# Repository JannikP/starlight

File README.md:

# starlight
Art installation to showcase our stellar neighborhood

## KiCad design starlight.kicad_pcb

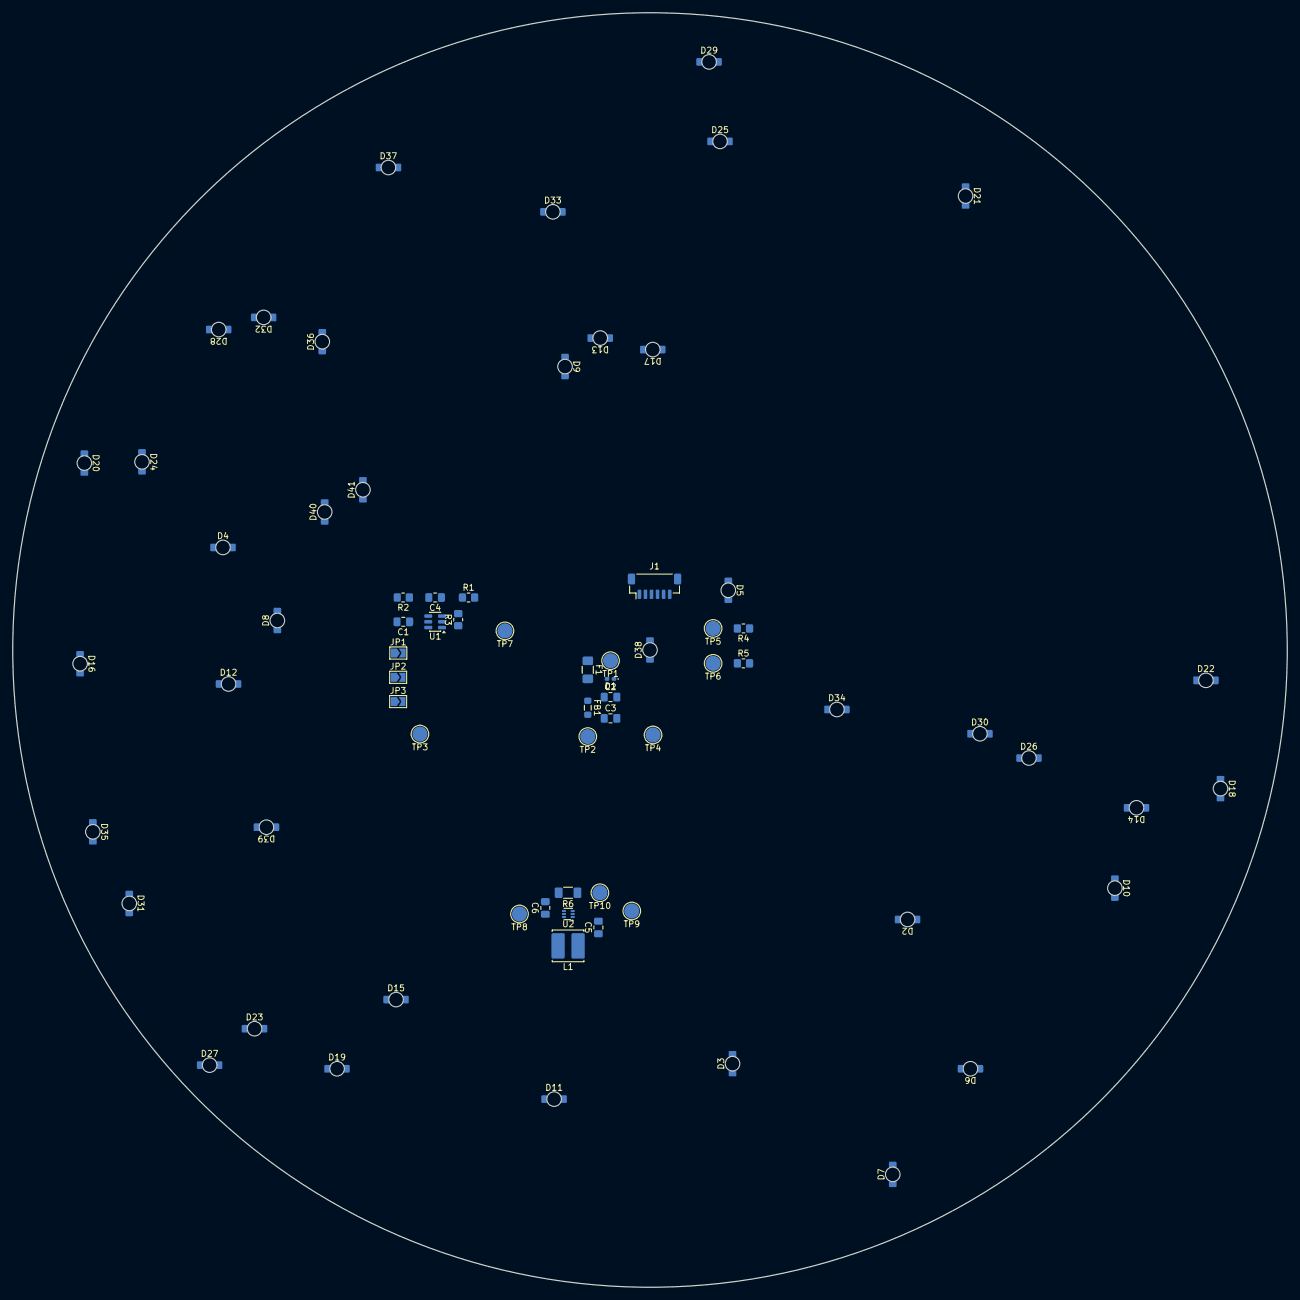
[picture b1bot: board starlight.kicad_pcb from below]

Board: 2 copper layers, 210.0 x 210.0 mm, 72 parts (72 on the bottom side), 50 nets, no tracks yet.

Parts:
C1, C2: 100n; C_0805_2012Metric_Pad1.18x1.45mm_HandSolder
C3, C5: 4µ7; C_0805_2012Metric_Pad1.18x1.45mm_HandSolder
C4: TBD; C_0805_2012Metric_Pad1.18x1.45mm_HandSolder
C6: 1µ; C_0805_2012Metric_Pad1.18x1.45mm_HandSolder
D1: 6V Clamp; D_0402_1005Metric_Pad0.77x0.64mm_HandSolder
D2, D3, D4, D5, D6, D7, D8, D9, D10, D11, D12, D13, D14, D15, D16, D17, D18, D19, D20, D21, D22, D23, D24, D25, D26, D27, D28, D29, D30, D31, D32, D33, D34, D35, D36, D37, D38, D39, D40, D41: Yellow; IN-S124AR-bottom-view
F1: Fuse; Fuse_1206_3216Metric_Pad1.42x1.75mm_HandSolder
FB1: 120 Ohm; L_0805_2012Metric_Pad1.05x1.20mm_HandSolder
J1: Conn_01x06; JST_SH_BM06B-SRSS-TB_1x06-1MP_P1.00mm_Vertical
JP1: 15 minutes; SolderJumper-2_P1.3mm_Open_TrianglePad1.0x1.5mm
JP2: 60 minutes; SolderJumper-2_P1.3mm_Open_TrianglePad1.0x1.5mm
JP3: Infinity; SolderJumper-2_P1.3mm_Open_TrianglePad1.0x1.5mm
L1: 10µ; L_Cenker_CKCS5040
R1: 4k7; R_0805_2012Metric_Pad1.20x1.40mm_HandSolder
R2: TBD; R_0805_2012Metric_Pad1.20x1.40mm_HandSolder
R3: 100k; R_0805_2012Metric_Pad1.20x1.40mm_HandSolder
R4, R5: 5k1; R_0805_2012Metric_Pad1.20x1.40mm_HandSolder
R6: 5; R_1206_3216Metric_Pad1.30x1.75mm_HandSolder
TP1: +5V_IN; TestPoint_Pad_D2.5mm
TP2: +5V; TestPoint_Pad_D2.5mm
TP3: Time; TestPoint_Pad_D2.5mm
TP4: GND; TestPoint_Pad_D2.5mm
TP5: CC1; TestPoint_Pad_D2.5mm
TP6: CC2; TestPoint_Pad_D2.5mm
TP7, TP9: Enable; TestPoint_Pad_D2.5mm
TP8: LED-Power; TestPoint_Pad_D2.5mm
TP10: FB; TestPoint_Pad_D2.5mm
U1: AT42QT1012-T; SOT-23-6
U2: TPS923610DRLR; SOT-563

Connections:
+5V: C1.1, C3.1, C5.1, FB1.2, JP1.1 (A), L1.1, TP2.1 (1_1), U1.5 (VDD), U2.1 (VIN)
/+5V_FUSED: C2.1, D1.2 (A2), F1.2, FB1.1
/+5V_IN: F1.1, J1.1, TP1.1 (1_1)
/CC1: J1.4, R4.2, TP5.1 (1_1)
/CC2: J1.3, R5.1, TP6.1 (1_1)
/EN_IN: J1.6, TP9.1 (1_1), U2.2 (ADIM)
/EN_OUT: J1.5, JP2.1 (A), R3.1, TP7.1 (1_1), U1.1 (OUT)
/FB: D38.1 (K), D39.1 (K), D40.1 (K), D41.1 (K), R6.1, TP10.1 (1_1), U2.3 (FB)
/LED_PWR: C6.1, D2.2 (A), D3.2 (A), D4.2 (A), D5.2 (A), TP8.1 (1_1), U2.5 (VOUT)
/SNS: C4.2, R2.1, U1.4 (SNS)
/SNSK: C4.1, R1.1, U1.3 (SNSK)
/TIME: JP1.2 (B), JP2.2 (B), JP3.2 (B), TP3.1 (1_1), U1.6 (TIME)
GND: C1.2, C2.2, C3.2, C5.2, C6.2, D1.1 (A1), J1.2, JP3.1 (A), R2.2, R3.2, R4.1, R5.2, R6.2, TP4.1 (1_1), U1.2 (VSS), U2.4 (GND)
unnamed: D2.1 (K), D6.2 (A)
unnamed: D3.1 (K), D7.2 (A)
unnamed: D4.1 (K), D8.2 (A)
unnamed: D5.1 (K), D9.2 (A)
unnamed: D6.1 (K), D10.2 (A)
unnamed: D10.1 (K), D14.2 (A)
unnamed: D7.1 (K), D11.2 (A)
unnamed: D11.1 (K), D15.2 (A)
unnamed: D8.1 (K), D12.2 (A)
unnamed: D12.1 (K), D16.2 (A)
unnamed: D9.1 (K), D13.2 (A)
unnamed: D13.1 (K), D17.2 (A)
unnamed: D14.1 (K), D18.2 (A)
unnamed: D15.1 (K), D19.2 (A)
unnamed: D16.1 (K), D20.2 (A)
unnamed: D17.1 (K), D21.2 (A)
unnamed: D18.1 (K), D22.2 (A)
unnamed: D19.1 (K), D23.2 (A)
unnamed: D20.1 (K), D24.2 (A)
unnamed: D21.1 (K), D25.2 (A)
unnamed: D22.1 (K), D26.2 (A)
unnamed: D23.1 (K), D27.2 (A)
unnamed: D24.1 (K), D28.2 (A)
unnamed: D25.1 (K), D29.2 (A)
unnamed: D26.1 (K), D30.2 (A)
unnamed: D27.1 (K), D31.2 (A)
unnamed: D28.1 (K), D32.2 (A)
unnamed: D29.1 (K), D33.2 (A)
unnamed: D30.1 (K), D34.2 (A)
unnamed: D31.1 (K), D35.2 (A)
unnamed: D32.1 (K), D36.2 (A)
unnamed: D33.1 (K), D37.2 (A)
unnamed: D34.1 (K), D38.2 (A)
unnamed: D35.1 (K), D39.2 (A)
unnamed: D36.1 (K), D40.2 (A)
unnamed: D37.1 (K), D41.2 (A)
unnamed: L1.2, U2.6 (SW)

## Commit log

2026-06-13 Converted the [list from Wikipedia](https://en.wikipedia.org/wiki/List_of_nearest_stars) to .csv using Claude Sonnet 4.6. Validation required!
2026-06-14 Selected key components and create the schematic for the on/off touch button.
2026-06-15 Selected 40 stars and derived PCB coordinates with a Python script.
2026-06-15 Schematic for the LEDs and LED-driver
2026-06-16 Power input protection circuit.
2026-06-21 Finished schematic and started PCB layout.
2026-06-21 Placed all LEDs at stars' locations using a Python script.
